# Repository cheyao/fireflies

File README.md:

# Fireflies

Firefly PCBs powered by the CH32V003.

These boards periodically flashes a xenon flash based on a timer, which gets accelerated when it detects flashes from surrounding PCBs.

There are currently 2 flash-detection circuits undergoing testing:

1. A reverse-biased diode using the ch32v003's internal OPA & ADC for sampling

2. A I2C ambiant light sensor for more "advanced" applications

The flash trigger isolates the hi-voltage trigger and the low-voltage circuitarry with a triac circuit, and uses a mosfet to trigger the flash.

### Features:

- Dual light-sensor: one via i2c, one via photodiode
- USB via ch32usb
- 7 seg for number display
- Flash activation circuit (high voltage)
- Programming ports

### Usage

Check firmware folder

Here's an example output for detection light intensity with the photodiode:

It's reverse-biased btw

### Schematic

### Programming

Check diagram:

### BOM

| Item | Price |  Where |
|---|---|----|
|PCB| 4$| elecrow|
|Stencil| 2$| elecrow|
|Components (check hardware bom)| $30| lcsc|
|Shipping| varies by region| none|

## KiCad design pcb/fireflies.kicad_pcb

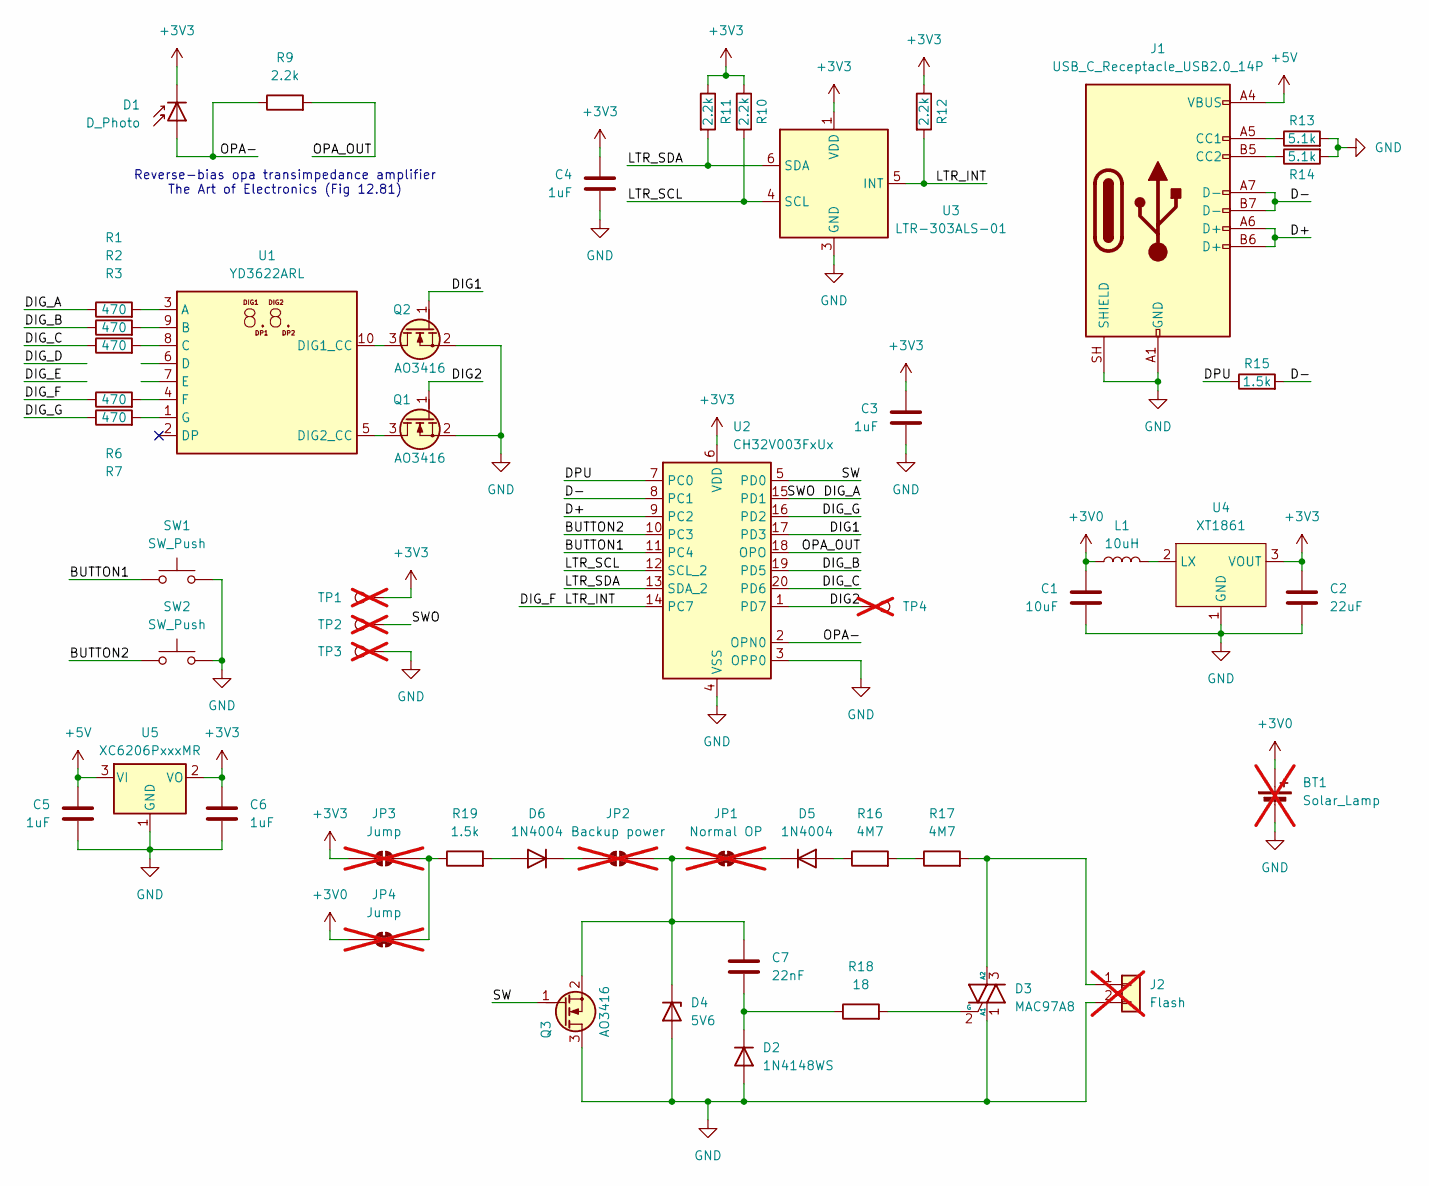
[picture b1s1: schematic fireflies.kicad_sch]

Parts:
BT1: Solar_Lamp; SolderWire-0.5sqmm_1x02_P4.6mm_D0.9mm_OD2.1mm_Relief; not fitted
C1: 10uF; C_0402_1005Metric; LCSC Part # C15525
C2: 22uF; C_0603_1608Metric; LCSC Part # C59461
C3, C4, C5, C6: 1uF; C_0402_1005Metric; LCSC Part # C52923
C7: 22nF; C_0402_1005Metric; LCSC Part # C5137627
D1: D_Photo; Photodiode_PD70-01C; LCSC Part # C131196
D2: 1N4148WS; D_SOD-323; LCSC Part # C2904852
D3: MAC97A8; SOT-23-3; LCSC Part # C2831929
D4: 5V6; D_SOD-123; LCSC Part # C173406
D5, D6: 1N4004; D_SOD-123F; LCSC Part # C162734
J1: USB_C_Receptacle_USB2.0_14P; USB_C_Receptacle_SHOU_HAN_16PIN_2MD; LCSC Part # C2765186
J2: Flash; SolderWire-0.5sqmm_1x02_P4.6mm_D0.9mm_OD2.1mm_Relief; not fitted
JP1: Normal OP; SolderJumper-2_P1.3mm_Bridged_RoundedPad1.0x1.5mm; not fitted
JP2: Backup power; SolderJumper-2_P1.3mm_Open_RoundedPad1.0x1.5mm; not fitted
JP3: Jump; SolderJumper-2_P1.3mm_Open_RoundedPad1.0x1.5mm; not fitted
JP4: Jump; SolderJumper-2_P1.3mm_Bridged_RoundedPad1.0x1.5mm; not fitted
L1: 10uH; L_0603_1608Metric; LCSC Part # C281107
Q1, Q2, Q3: AO3416; SOT-23; LCSC Part # C347499
R1, R2, R3, R6, R7: 470; R_0402_1005Metric; LCSC Part # C25117
R9, R10, R11, R12: 2.2k; R_0402_1005Metric; LCSC Part # C25879
R13, R14: 5.1k; R_0402_1005Metric; LCSC Part # C25905
R15, R19: 1.5k; R_0402_1005Metric; LCSC Part # C25867
R16, R17: 4M7; R_0402_1005Metric; LCSC Part # C3013173
R18: 18; R_0603_1608Metric; LCSC Part # C2933165
SW1, SW2: SW_Push; SW_Push_SPST_TSA016; LCSC Part # C2888430
TP1, TP2, TP3, TP4: TestPoint; TestPoint_Pad_D1.0mm; not fitted
U1: YD3622ARL; YD3622A; LCSC Part # C46614038
U2: CH32V003FxUx; QFN-20-1EP_3x3mm_P0.4mm_EP1.65x1.65mm_ThermalVias; LCSC Part # C5299908
U3: LTR-303ALS-01; Lite-On_LTR-303ALS-01; LCSC Part # C492382
U4: XT1861; SOT-23-3; LCSC Part # C236396
U5: XC6206PxxxMR; SOT-23-3; LCSC Part # C347376

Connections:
+3V0: BT1.1 (+), C1.1, JP4.1 (A), L1.1
+3V3: C2.1, C3.1, C4.1, C6.1, D1.1 (K), JP3.1 (A), R10.1, R11.1, R12.1, TP1.1 (1_1), U2.6 (VDD), U3.1 (VDD), U4.3 (VOUT), U5.2 (VO)
+5V: C5.1, J1.A4 (VBUS), J1.A9 (VBUS), J1.B4 (VBUS), J1.B9 (VBUS), U5.3 (VI)
/BUTTON1: SW1.1, U2.11 (PC4)
/BUTTON2: SW2.1, U2.10 (PC3)
/D+: J1.A6 (D+), J1.B6 (D+), U2.9 (PC2)
/D-: J1.A7 (D-), J1.B7 (D-), R15.2, U2.8 (PC1)
/DIG1: Q2.1 (G), U2.17 (PD3)
/DIG2: Q1.1 (G), TP4.1 (1_1), U2.1 (PD7)
/DIG_A: R1.1, TP2.1 (1_1), U2.15 (PD1)
/DIG_B: R2.1, U2.19 (PD5)
/DIG_C: R3.1, U2.20 (PD6)
/DIG_F: R6.1, R12.2, U2.14 (PC7), U3.5 (INT)
/DIG_G: R7.1, U2.16 (PD2)
/DPU: R15.1, U2.7 (PC0)
/LTR_SCL: R10.2, U2.12 (SCL_2), U3.4 (SCL)
/LTR_SDA: R11.2, U2.13 (SDA_2), U3.6 (SDA)
/OPA-: D1.2 (A), R9.1, U2.2 (OPN0)
/OPA_OUT: R9.2, U2.18 (OPO)
/SW: Q3.1 (G), U2.5 (PD0)
GND: BT1.2 (-), C1.2, C2.2, C3.2, C4.2, C5.2, C6.2, D2.2 (A), D3.1 (A1), D4.2 (A), J1.A1 (GND), J1.A12 (GND), J1.B1 (GND), J1.B12 (GND), J1.SH (SHIELD), J2.2, Q1.2 (S), Q2.2 (S), Q3.3 (D), R13.2, R14.2, SW1.2, SW2.2, TP3.1 (1_1), U2.3 (OPP0), U2.4 (VSS), U2.21 (VSS), U3.3 (GND), U4.1 (GND), U5.1 (GND)
unnamed: C7.2, D2.1 (K), R18.1
unnamed: D3.3 (A2), J2.1, R17.2
unnamed: D3.2 (G), R18.2
unnamed: C7.1, D4.1 (K), JP1.1 (A), JP2.2 (B), Q3.2 (S)
unnamed: D5.2 (A), R16.1
unnamed: D5.1 (K), JP1.2 (B)
unnamed: D6.2 (A), R19.2
unnamed: D6.1 (K), JP2.1 (A)
unnamed: J1.A5 (CC1), R13.1
unnamed: J1.B5 (CC2), R14.1
unnamed: JP3.2 (B), JP4.2 (B), R19.1
unnamed: Q1.3 (D), U1.5 (DIG2_CC)
unnamed: Q2.3 (D), U1.10 (DIG1_CC)
unnamed: R16.2, R17.1
unnamed: R1.2, U1.3 (A)
unnamed: R2.2, U1.9 (B)
unnamed: R3.2, U1.8 (C)
unnamed: R6.2, U1.4 (F)
unnamed: R7.2, U1.1 (G)
unnamed: L1.2, U4.2 (LX)

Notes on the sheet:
Reverse-bias opa transimpedance amplifier The Art of Electronics (Fig 12.81)

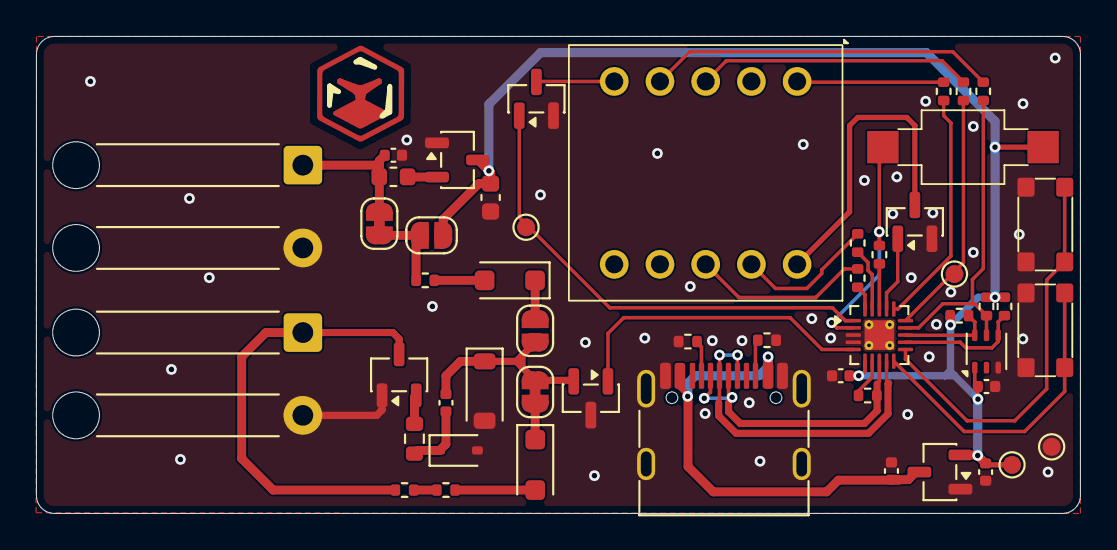
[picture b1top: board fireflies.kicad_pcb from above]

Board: 2 copper layers, 58.0 x 26.5 mm, 51 parts (0 on the bottom side), 41 nets.

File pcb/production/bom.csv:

Designator,Footprint,Quantity,Value,LCSC Part #
C1,0402,1,10uF,C15525
C2,0603,1,22uF,C59461
"C3, C4, C5, C6",0402,4,1uF,C52923
C7,0402,1,22n,C5137468
D1,Photodiode_PD70-01C,1,D_Photo,C131196
D2,D_SOD-323,1,1N4148WS,C2904852
D3,SOT-23-3,1,MAC97A8,C2831929
D4,D_SOD-123,1,5V6,C173406
"D5, D6",D_SOD-123F,2,1N4004,C162734
J1,USB_C_Receptacle_SHOU_HAN_16PIN_2MD,1,USB_C_Receptacle_USB2.0_14P,C2765186
L1,0603,1,10uH,C281107
"Q1, Q2, Q3",SOT-23,3,AO3416,C347499
"R1, R2, R3, R6, R7",0402,5,470,C25117
"R10, R11, R12, R9",0402,4,2.2k,C25879
"R13, R14",0402,2,5.1k,C25905
"R15, R19",0402,2,1.5k,C25867
"R16, R17",0402,2,4M7,C3013173
R18,0603,1,18,C2933165
"SW1, SW2",SW_Push_SPST_TSA016,2,SW_Push,C2888430
U1,YD3622A,1,YD3622ARL,C46614038
U2,QFN-20-1EP_3x3mm_P0.4mm_EP1.65x1.65mm_ThermalVias,1,CH32V003FxUx,C5299908
U3,Lite-On_LTR-303ALS-01,1,LTR-303ALS-01,C492382
U4,SOT-23-3,1,XT1861,C236396
U5,SOT-23-3,1,XC6206PxxxMR,C347376

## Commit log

2026-05-12 Init
2026-06-01 Opps didn't push hardware
2026-06-01 Improve
2026-06-03 Hardware i2c stub
2026-06-07 Sensor I2C
